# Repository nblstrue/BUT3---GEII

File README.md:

# Electro-Acoustic Guitar

A last-year degree electronic project that consists of creating a guitar that can be played manually and automatically.

## Version 1 - Code for the Prototype A

- Frequency Meter for ajusting the notes of the cords;
- Conception of an Automatic Mode sending a PMW signal;
- Exit function stopping the process of the program.

## Version 2 - Beginning of the automated mode
- Uses the frequency to move a step by step motor (specifications not available at the moment);
- Bypassing some display sub functions for speeding the process.

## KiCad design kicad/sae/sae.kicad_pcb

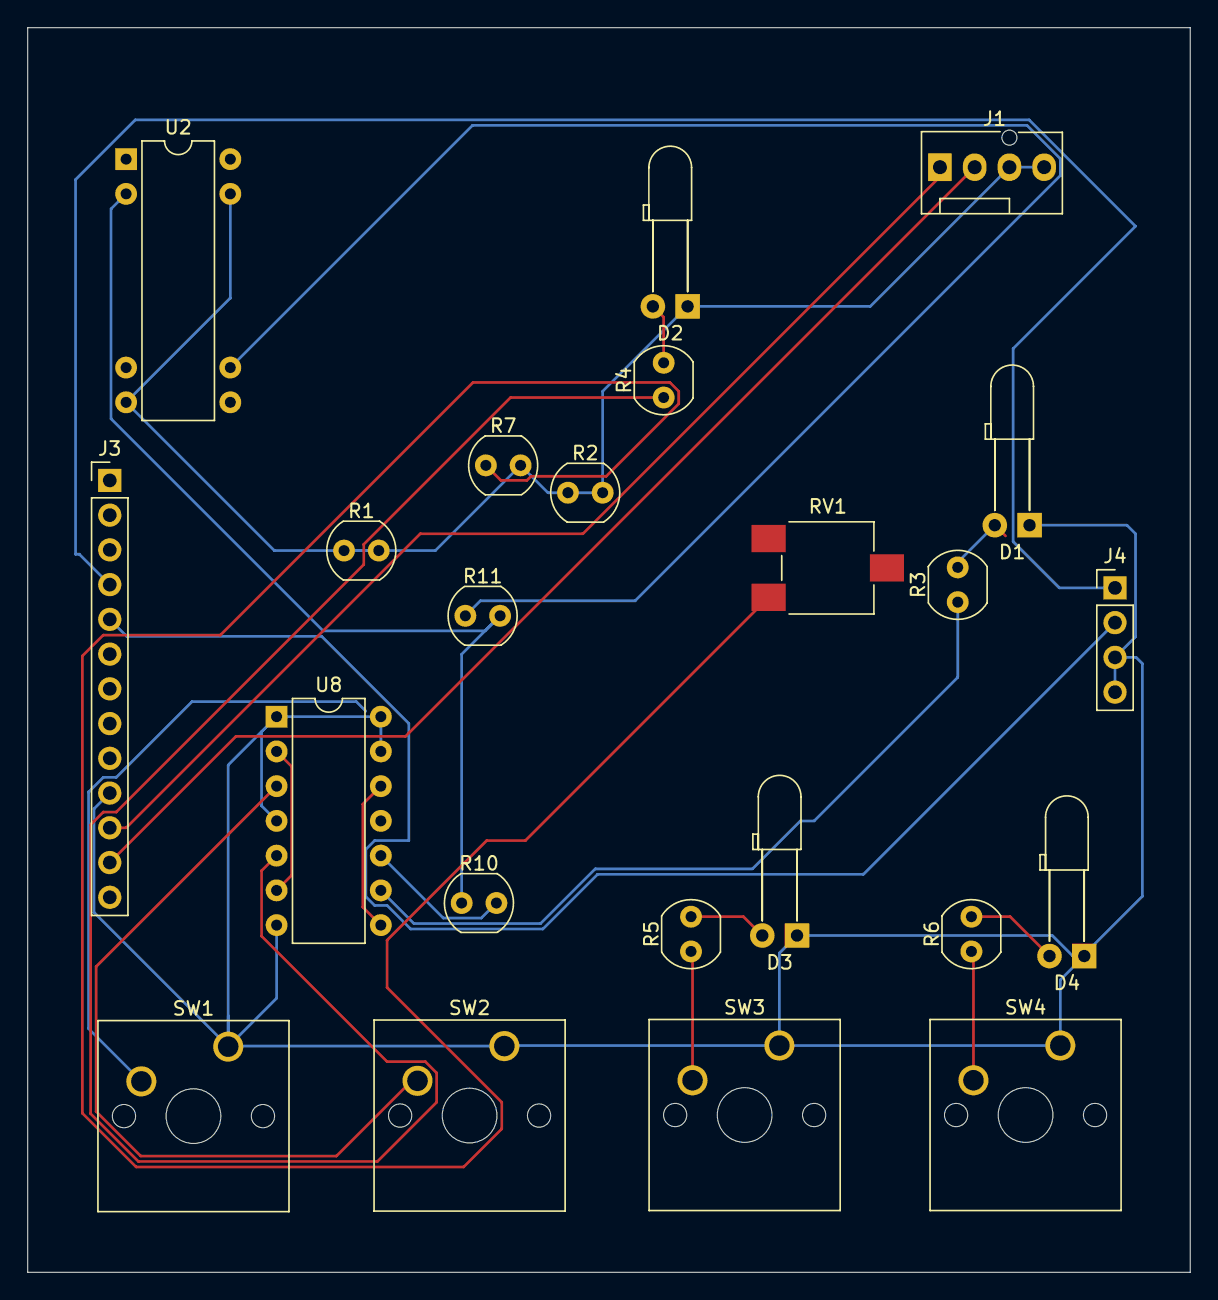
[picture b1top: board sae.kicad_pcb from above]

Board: 2 copper layers, 85.0 x 91.0 mm, 23 parts (0 on the bottom side), 20 nets.

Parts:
D1, D2, D3, D4: LED; LED_D3.0mm_Horizontal_O6.35mm_Z10.0mm
J1: GME128128_i2c; FanPinHeader_1x04_P2.54mm_Vertical
J3: Conn_01x13_Pin; PinHeader_1x13_P2.54mm_Vertical
J4: Conn_01x04_Pin; PinHeader_1x04_P2.54mm_Vertical
R1, R2: 10k; R_LDR_4.9x4.2mm_P2.54mm_Vertical
R3, R4, R5, R6, R7, R10, R11: R; R_LDR_4.9x4.2mm_P2.54mm_Vertical
RV1: 1k; Potentiometer_ACP_CA6-VSMD_Vertical
SW1, SW2, SW3, SW4: SW_Push; SW_Cherry_MX_1.00u_PCB
U2: TL081; DIP-8-16_W7.62mm
U8: 74HC74; DIP-14_W7.62mm

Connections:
/ANUL_button: R4.1, U8.5 (Q)
/DOWN_button: R6.1, SW4.2
/GND: D1.1 (K), D2.1 (K), D3.1 (K), D4.1 (K), J1.3, J1.4, J3.10, J3.13, J4.3, J4.4, R1.1, R1.2, R2.1, R2.2, R7.2, R10.2, SW1.1, SW2.1, SW3.1, SW4.1, U2.4 (V-), U2.7 (V+), U8.1 (~R), U8.4 (~S), U8.7 (GND), U8.10 (~S), U8.13 (~R), U8.14 (VCC)
/OK_button: R3.1, U8.9 (Q)
/SCL: J1.2, J3.12
/SDA: J1.1, J3.11
/UP_button: R5.1, SW3.2
/dirPin: J3.4, J4.1
/stepPin: J3.5, J4.2
unnamed: D1.2 (A), R3.2
unnamed: D2.2 (A), R4.2
unnamed: D3.2 (A), R5.2
unnamed: D4.2 (A), R6.2
unnamed: R7.1, RV1.1
unnamed: R11.1, U2.6
unnamed: R10.1, R11.2, U2.2 (-)
unnamed: SW2.2, U8.3 (C)
unnamed: U8.2 (D), U8.6 (~Q)
unnamed: SW1.2, U8.11 (C)
unnamed: U8.8 (~Q), U8.12 (D)

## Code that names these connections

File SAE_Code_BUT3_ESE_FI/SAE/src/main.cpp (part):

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#include <Adafruit_GFX.h>
#include <Adafruit_SH110X.h>

#define OK_BUTTON           D2
#define LED                 D3
#define ANL_BUTTON          D4
#define dirPin              D5
#define stepPin             D6
#define UP_BUTTON           D7
#define DOWN_BUTTON         D8
#define FREQUENCE_PIN       D12
#define BATTERY_PIN         D13
#define SCREEN_WIDTH        128  // display display width, in pixels
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{
  Serial.begin(115200);

  pinMode(DOWN_BUTTON, INPUT);
  pinMode(UP_BUTTON, INPUT);
  pinMode(ANL_BUTTON, INPUT);
  pinMode(OK_BUTTON, INPUT);
  pinMode(LED, OUTPUT);
  pinMode(FREQUENCE_PIN, INPUT);
  GME128128_begin(SCREEN_ADRESS);
  pinMode(stepPin, OUTPUT);
  pinMode(dirPin, OUTPUT);

  while(!digitalRead(DOWN_BUTTON))
    Frequence();
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    
    if(freq > frequency_notes[freq_mem]*1.05)
    {
        digitalWrite(dirPin, HIGH);
        for(int i = 0; i < 1000; i++)
        {
            digitalWrite(stepPin, HIGH);
            delayMicroseconds(4300);
            digitalWrite(stepPin, LOW);
            delayMicroseconds(4300);
            if(freq == frequency_notes[freq_mem])
                break;
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    else{
        if(freq < frequency_notes[freq_mem]*0.95)
        {
            digitalWrite(dirPin, LOW);
            for(int i = 0; i < 1000; i++)
            {
                digitalWrite(stepPin, HIGH);
                delayMicroseconds(4300);
                digitalWrite(stepPin, LOW);
                delayMicroseconds(4300);
                if(freq == frequency_notes[freq_mem])
                    break;
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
